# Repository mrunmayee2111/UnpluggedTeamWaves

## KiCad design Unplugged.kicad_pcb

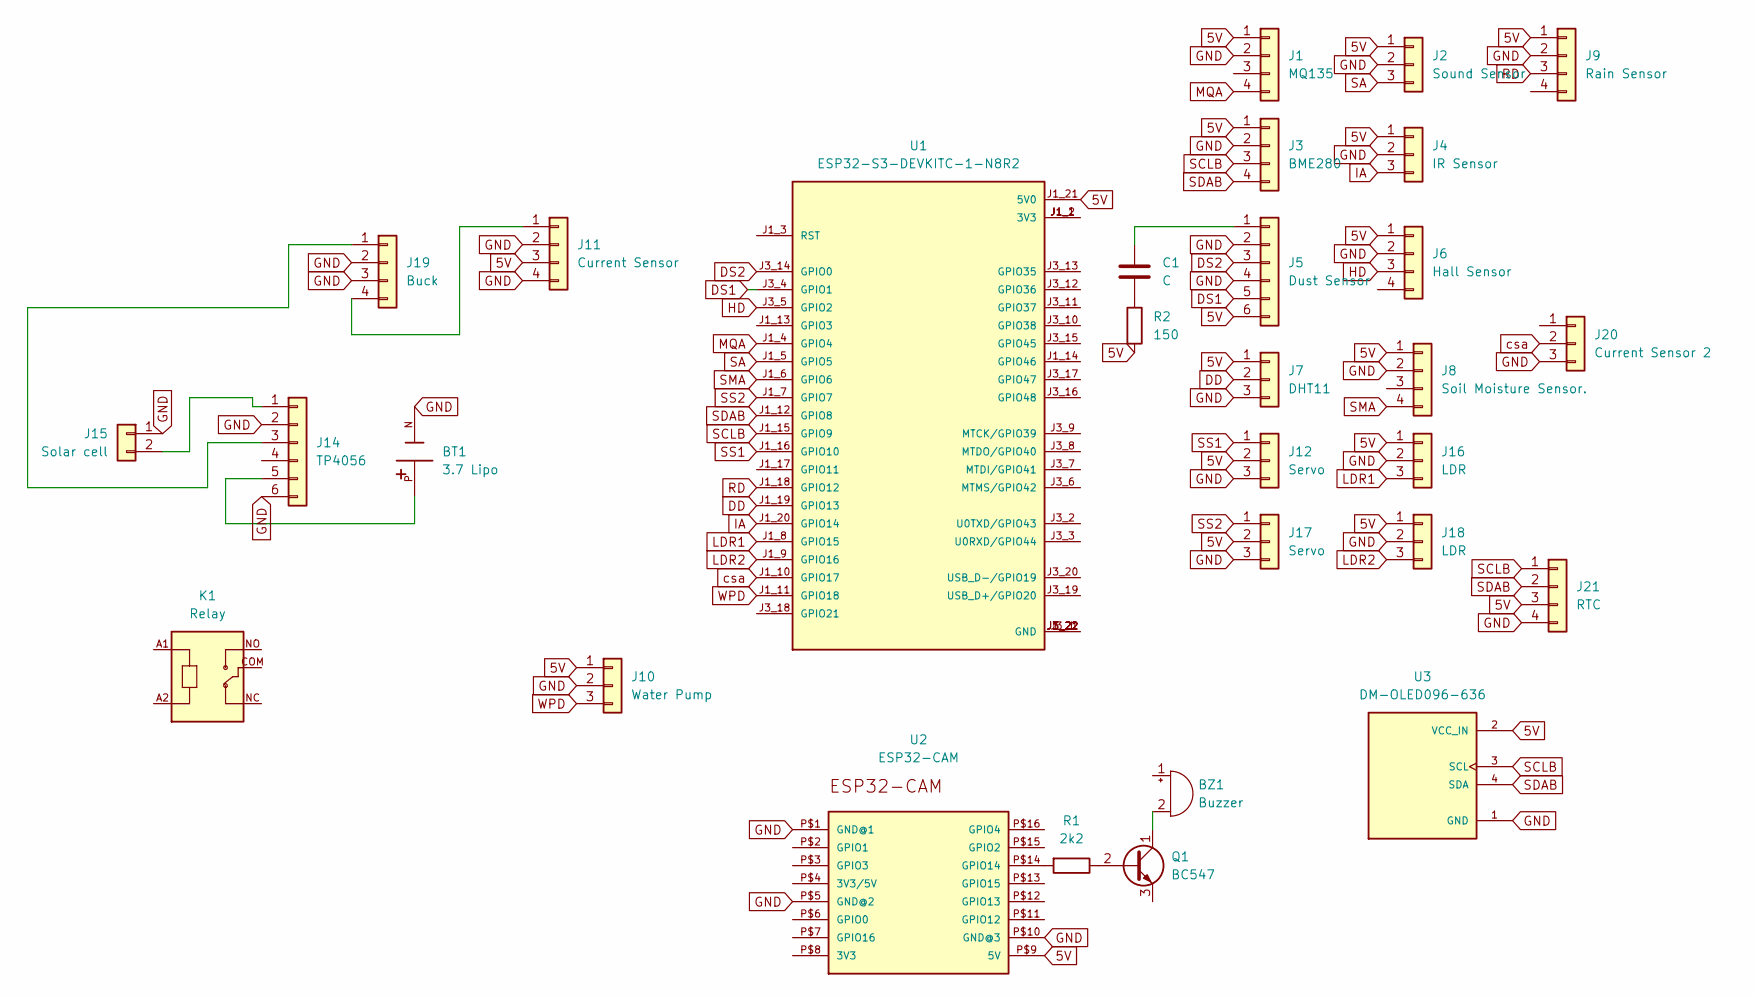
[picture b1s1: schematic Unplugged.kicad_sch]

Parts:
BT1: 3.7 Lipo; BAT_BH-18650-PC; PARTREV 05/17/19
BZ1: Buzzer; Buzzer_12x9.5RM7.6
C1: C; C_Disc_D3.0mm_W1.6mm_P2.50mm
J1: MQ135; PinSocket_1x04_P1.00mm_Vertical
J2: Sound Sensor; PinSocket_1x03_P1.00mm_Vertical
J3: BME280; PinSocket_1x04_P1.00mm_Vertical
J4: IR Sensor; PinSocket_1x03_P1.00mm_Vertical
J5: Dust Sensor; PinSocket_1x06_P1.00mm_Vertical
J6: Hall Sensor; PinSocket_1x04_P1.00mm_Vertical
J7: DHT11; PinSocket_1x03_P1.00mm_Vertical
J8: Soil Moisture Sensor.; PinSocket_1x04_P1.00mm_Vertical
J9: Rain Sensor; PinSocket_1x04_P1.00mm_Vertical
J10: Water Pump; PinSocket_1x03_P1.00mm_Vertical
J11: Current Sensor; PinSocket_1x04_P1.00mm_Vertical
J12, J17: Servo; PinSocket_1x03_P1.00mm_Vertical
J14: TP4056
J15: Solar cell; AMASS_XT30U-F_1x02_P5.0mm_Vertical
J16, J18: LDR; PinSocket_1x03_P1.00mm_Vertical
J19: Buck
J20: Current Sensor 2; PinSocket_1x03_P1.00mm_Vertical
J21: RTC; PinSocket_1x04_P1.00mm_Vertical
K1: Relay; RELAY_SRD-05VDC-SL-C
Q1: BC547; TO-92_Inline
R1: 2k2; R_Axial_DIN0204_L3.6mm_D1.6mm_P5.08mm_Vertical
R2: 150; R_Axial_DIN0204_L3.6mm_D1.6mm_P5.08mm_Vertical
U1: ESP32-S3-DEVKITC-1-N8R2; XCVR_ESP32-S3-DEVKITC-1-N8R2; PARTREV V1
U2: ESP32-CAM
U3: DM-OLED096-636; MODULE_DM-OLED096-636; PARTREV 2018-09-10

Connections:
5V: J1.1, J2.1, J3.1, J4.1, J5.6, J6.1, J7.1, J8.1, J9.1, J10.1, J11.3, J12.2, J16.1, J17.2, J18.1, J21.3, R2.2, U1.J1_21 (5V0), U2.P$9 (5V), U3.2 (VCC_IN)
DD: J7.2, U1.J1_19 (GPIO13)
DS1: J5.5, U1.J3_4 (GPIO1)
DS2: J5.3, U1.J3_14 (GPIO0)
GND: BT1.N, J1.2, J2.2, J3.2, J4.2, J5.2, J5.4, J6.2, J7.3, J8.2, J9.2, J10.2, J11.2, J11.4, J12.3, J14.2, J14.6, J15.1, J16.2, J17.3, J18.2, J19.2, J19.3, J20.3, J21.4, U2.P$1 (GND@1), U2.P$5 (GND@2), U2.P$10 (GND@3), U3.1 (GND)
HD: J6.3, U1.J3_5 (GPIO2)
IA: J4.3, U1.J1_20 (GPIO14)
LDR1: J16.3, U1.J1_8 (GPIO15)
LDR2: J18.3, U1.J1_9 (GPIO16)
MQA: J1.4, U1.J1_4 (GPIO4)
unnamed: BZ1.2 (-), Q1.1 (C)
unnamed: C1.2, R2.1
unnamed: C1.1, J5.1
unnamed: J11.1, J19.4
unnamed: J14.1, J15.2
unnamed: J14.3, J19.1
unnamed: BT1.P, J14.5
unnamed: Q1.2 (B), R1.1
unnamed: U1.J1_1 (3V3), U1.J1_2 (3V3)
unnamed: U1.J1_22 (GND), U1.J3_1 (GND), U1.J3_21 (GND), U1.J3_22 (GND)
unnamed: R1.2, U2.P$14 (GPIO14)
RD: J9.3, U1.J1_18 (GPIO12)
SA: J2.3, U1.J1_5 (GPIO5)
SCLB: J3.3, J21.1, U1.J1_15 (GPIO9), U3.3 (SCL)
SDAB: J3.4, J21.2, U1.J1_12 (GPIO8), U3.4 (SDA)
SMA: J8.4, U1.J1_6 (GPIO6)
SS1: J12.1, U1.J1_16 (GPIO10)
SS2: J17.1, U1.J1_7 (GPIO7)
WPD: J10.3, U1.J1_11 (GPIO18)
csa: J20.2, U1.J1_10 (GPIO17)

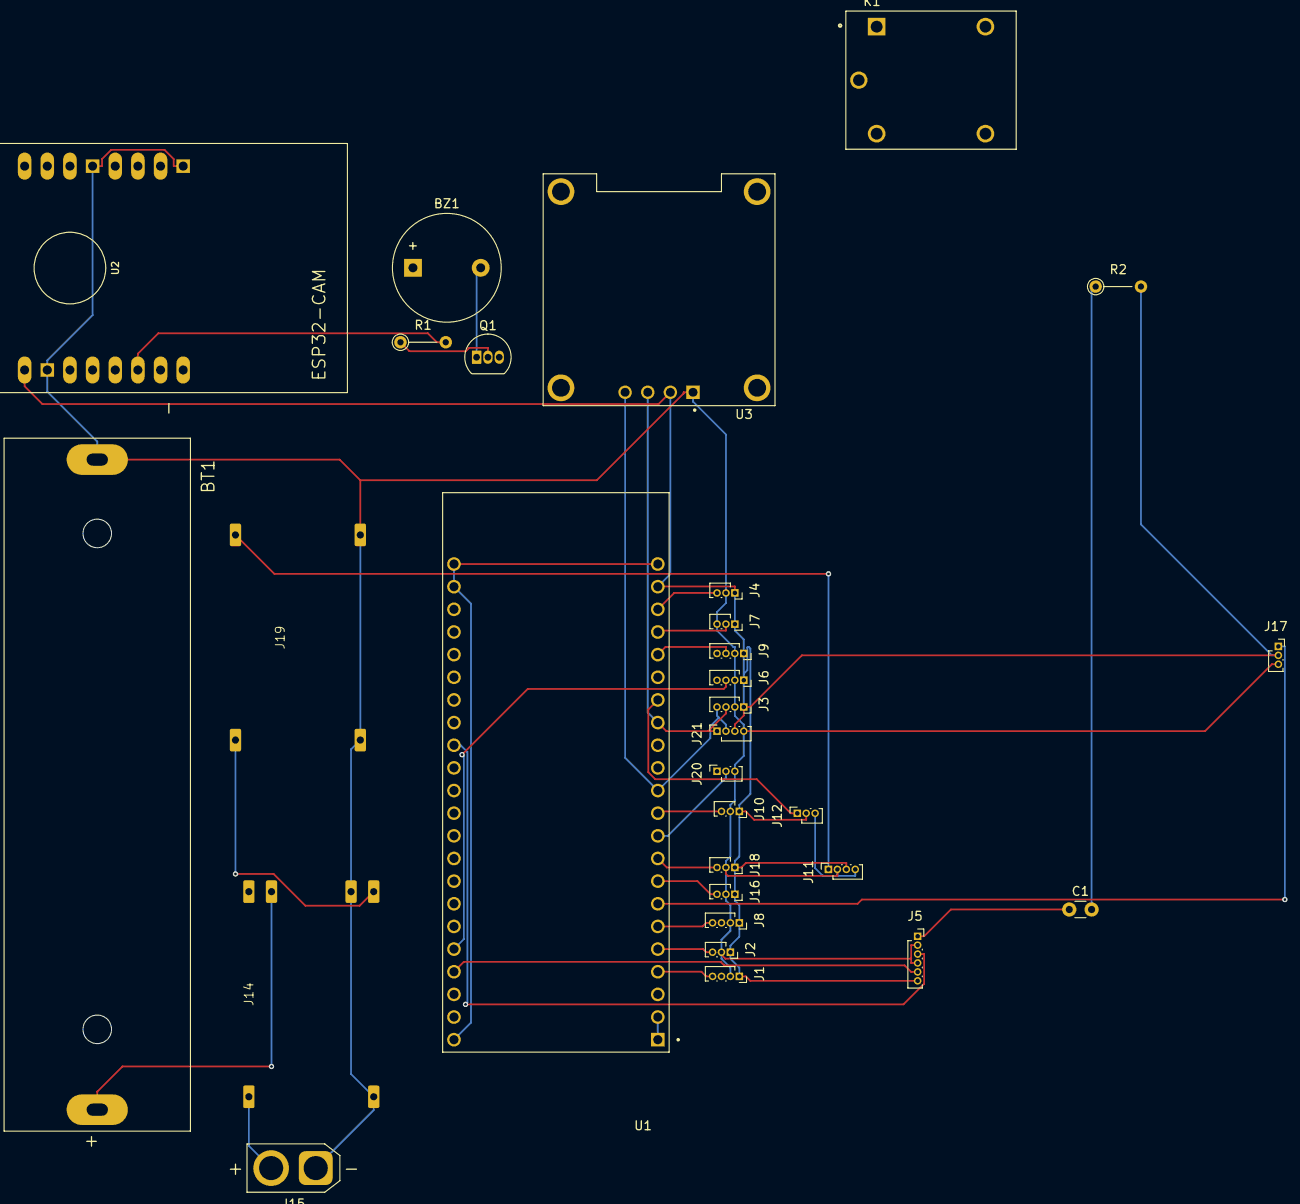
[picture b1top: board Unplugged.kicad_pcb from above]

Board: 2 copper layers, 30 parts (0 on the bottom side), 30 nets.
